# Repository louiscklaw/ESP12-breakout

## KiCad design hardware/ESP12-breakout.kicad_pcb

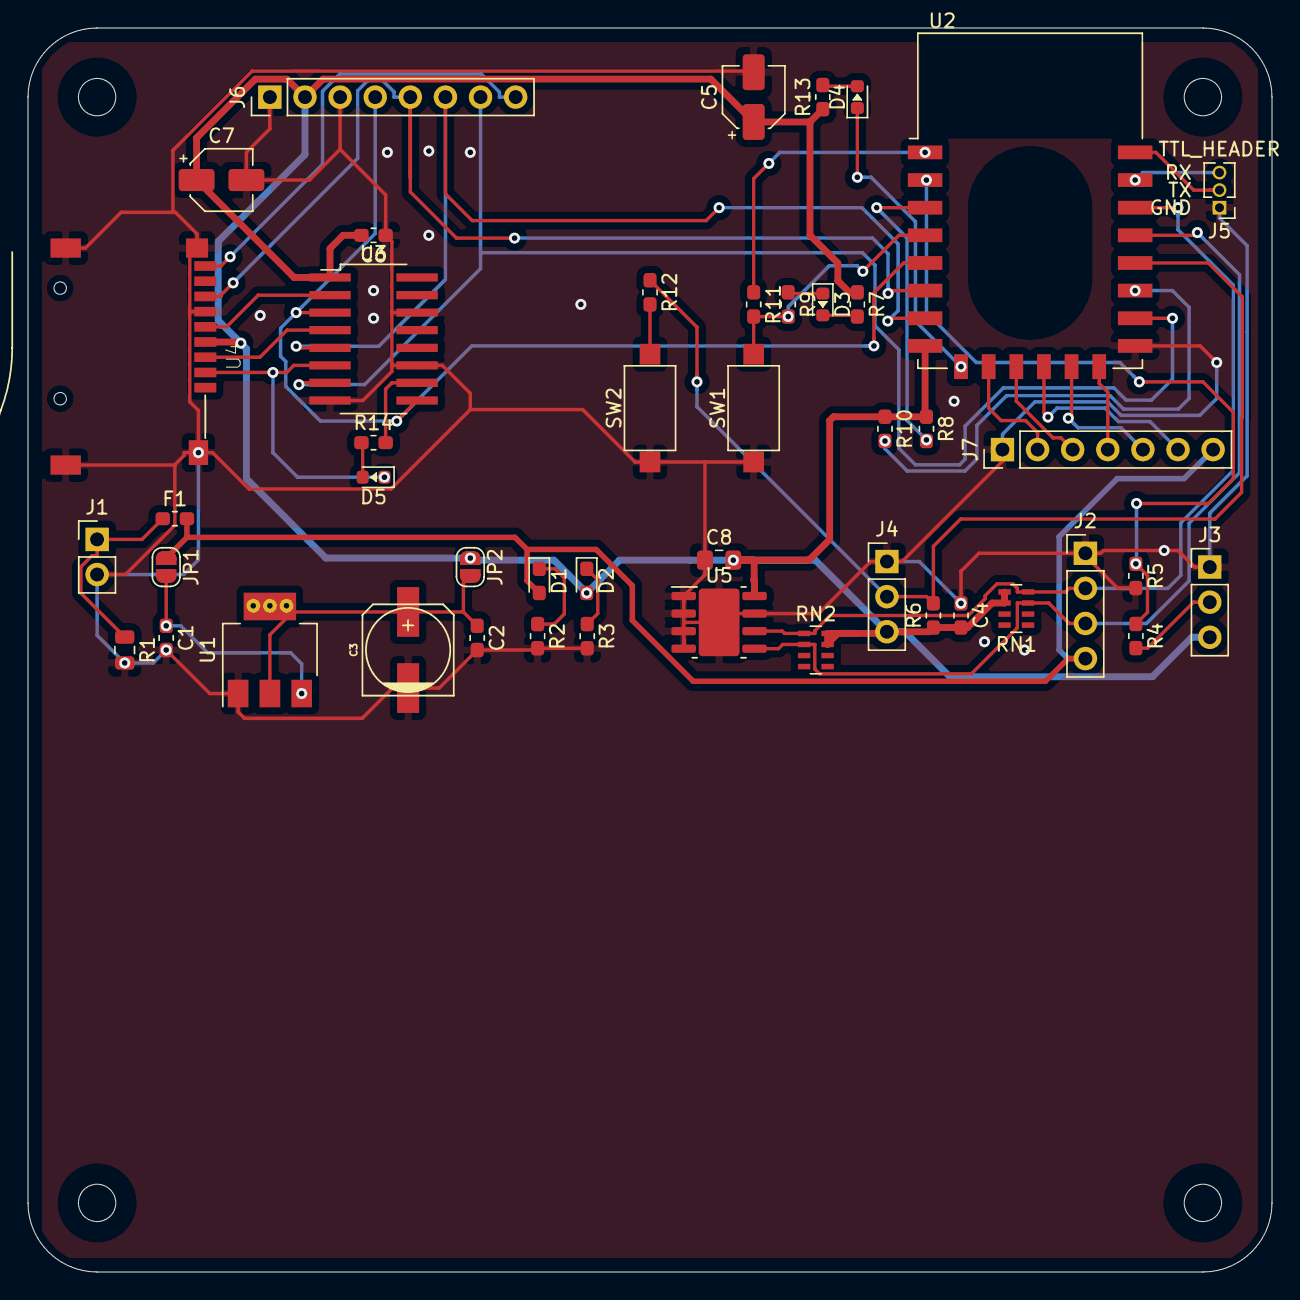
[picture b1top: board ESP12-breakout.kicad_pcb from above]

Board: 2 copper layers, 90.0 x 90.0 mm, 50 parts (0 on the bottom side), 39 nets.

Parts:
C1, C2: C104,0603; C_0603_1608Metric_Pad1.05x0.95mm_HandSolder
C3: CP47uf,50V; c_elec_6.3x7.7
C4, C6: C106,0603; C_0603_1608Metric_Pad1.05x0.95mm_HandSolder
C5: CP10uf,16V; CP_Elec_4x5.3
C7: CP1uf,50V; CP_Elec_4x5.3
C8: C106,0805; C_0805_2012Metric_Pad1.15x1.40mm_HandSolder
D1: 5V; LED_0603_1608Metric_Pad1.05x0.95mm_HandSolder
D2: 3V3; LED_0603_1608Metric_Pad1.05x0.95mm_HandSolder
D3: LED_BLUE,0603; LED_0603_1608Metric
D4, D5: LED_GREEN,0603; LED_0603_1608Metric
F1: 500mA,0603; R_0603_1608Metric_Pad1.05x0.95mm_HandSolder
H1, H2, H3, H4: MOUNT_M2.5; MountingHole_2.7mm_M2.5,rpi_like
J1: Vin; PinHeader_1x02_P2.54mm_Vertical
J2: I2C; PinHeader_1x04_P2.54mm_Vertical
J3: ADC; PinHeader_1x03_P2.54mm_Vertical
J4: ONE_WIRE; PinHeader_1x03_P2.54mm_Vertical
J5: TTL_HEADER
J6: TF_HEADER; PinHeader_1x08_P2.54mm_Vertical
J7: IO; PinHeader_1x07_P2.54mm_Vertical
JP1: 5V_EN; SolderJumper-2_P1.3mm_Open_RoundedPad1.0x1.5mm
JP2: 3V3_EN; SolderJumper-2_P1.3mm_Open_RoundedPad1.0x1.5mm
R1: VAR_5V6,0805; VAR_0805
R2, R5: TBA,0603; R_0603_1608Metric_Pad1.05x0.95mm_HandSolder
R3, R4, R8, R10, R14: R102,0603; R_0603_1608Metric_Pad1.05x0.95mm_HandSolder
R6: R472,0603; R_0603_1608Metric_Pad1.05x0.95mm_HandSolder
R7, R11, R12: R471,0603; R_0603_1608Metric_Pad1.05x0.95mm_HandSolder
R9: R0,0603; R_0603_1608Metric_Pad1.05x0.95mm_HandSolder
R13: R561,0603; R_0603_1608Metric_Pad1.05x0.95mm_HandSolder
RN1, RN2: RN_472,0603; R_Array_Concave_4x0603
SW1, SW2: SW_RESET,2_leg,SMD; SW_SPST_CK_RS282G05A3
U1: AMS1117-3.3; AMS1117_SOT-223
U2: ESP-12E
U3: CD74HC4050; 74HCT4050_SOP16
U4: TF_CARD_SOCKET,SELF_EJECT; SUNTECH_ST-TF-003A
U5: 24C02_SOIC8; 24Cxx_SOIC8

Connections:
+3V3: C4.2, C5.1, C6.2, C7.1, C8.2, D2.2, J3.3, J4.3, J6.2, JP2.1, R6.1, R7.1, R8.1, R10.1, R13.1, RN1.5, RN1.6, RN2.7, RN2.8, U2.8, U3.1, U4.4, U5.8
+5V: D1.2, F1.2, J2.4, J7.7, JP1.1
/24c02/SCL: J2.2, RN1.4, RN2.1, U2.20, U5.6
/24c02/SDA: J2.3, RN1.3, RN2.2, U2.19, U5.5
/ESP-12E/ADC: R4.1, R5.1, U2.2
/ESP-12E/CS: J6.7, U2.16, U3.7
/ESP-12E/DATA: J4.2, R6.2, R12.1, U2.18
/ESP-12E/DEBUG_LED: D4.1, U2.9
/ESP-12E/EN: R8.2, U2.3
/ESP-12E/GPIO16: R9.2, R11.2, SW1.2, U2.4
/ESP-12E/IO1: J7.2, U2.10
/ESP-12E/IO2: J7.3, U2.11
/ESP-12E/IO3: J7.4, U2.14
/ESP-12E/IO4: J7.5, U2.13
/ESP-12E/IO5: J7.6, U2.12
/ESP-12E/RESET: R11.1, U2.1
/ESP-12E/RXD: J5.RX, U2.21
/ESP-12E/TXD: J5.TX, U2.22
/SDCARD/CD: J6.8, U4.9
/SDCARD/CLK: J6.4, U2.5, U3.3, U3.9
/SDCARD/DI: J6.6, U2.7, U3.5
/SDCARD/DO: J6.5, U2.6, U4.7
/SDCARD/O_CLK: U3.2, U4.5
/SDCARD/O_CS: D5.1, U3.6, U4.2
/SDCARD/O_DI: U3.4, U4.3
GND: C1.2, C2.2, C3.2, C4.1, C5.2, C6.1, C7.2, C8.1, J1.2, J2.1, J3.1, J4.1, J5.GND, J6.1, J6.3, J7.1, R1.2, R2.2, R3.2, R5.2, SW1.1, SW2.1, U1.1, U2.15, U3.8, U3.11, U3.14, U4.6, U4.G, U5.1, U5.2, U5.3, U5.4, U5.7
unnamed: C1.1, JP1.2, U1.3
unnamed: C2.1, C3.1, JP2.2, U1.2
unnamed: D1.1, R2.1
unnamed: D2.1, R3.1
unnamed: D3.1, R9.1
unnamed: D3.2, R7.2
unnamed: D4.2, R13.2
unnamed: D5.2, R14.1
unnamed: F1.1, J1.1, R1.1
unnamed: J3.2, R4.2
unnamed: R10.2, U2.17
unnamed: R12.2, SW2.2
unnamed: R14.2, U3.10

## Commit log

2019-06-04 init commit,
2019-06-05 update for reference image,
2019-06-05 update,
2019-06-05 update for DRC,
2019-06-05 update for 24C02,
2019-06-05 update for routing,
2019-06-05 update for routing, DRC ok,
2020-05-05 ci: init travis build config,
2020-05-05 ci: init travis token,
